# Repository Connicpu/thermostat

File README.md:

# Thermostat V3

Shared as-is — not seeking contributions or pull requests.

ESP32-C6 Zigbee thermostat for single-stage HVAC (R/C/W/Y/G), with e-paper display, SHT40 temperature/humidity sensor, and triac outputs. Designed for JLCPCB assembly.

## Gallery

On-device screens (296×128 e-paper, shown at 2×; °F):

| Home | Menu |
|---|---|
|  |  |
| **Schedule** | **Boost to** |
|  |  |

Home Assistant Lovelace card ([install](firmware/ha/lovelace-card/README.md)):

| Heat, day (light) | Cool, night (dark) | Timed heat boost (dark) |
|---|---|---|
|  |  |  |

More: case renders in [case/](case/), every menu screen in [firmware/README.md](firmware/README.md).

## Case

The case (`case/thermostat_case.scad`) is a 147 × 71 × 26.25 mm PETG shell, backplate, and panel carrier for a Bambu P2S with a 0.4 mm nozzle. The carrier holds the display panel with its nominal back 4.45 mm above the board. The panel rests on stops 0.15 mm under that, located by the long-edge fences and the cable-end posts. Four bridges in the shell press the border. The flex plugs into J4 with the display panel seated on the stops. A thin corner can leave J4; the shell comes off, the tail is pressed back in, and the slider is closed. A fingernail shuts the slider on the ear's +x face, and a fingertip on the carrier push opens it toward +x. The shell clips to the backplate. It does not clamp the board. The three buttons snap into the face from the inside and stay in the shell. Each cap is a 65° cone and one 0.40 mm leaf. The leaf is a cantilever, free length 4.35 mm, and it only keeps the cap in the face. The print adds a 0.34 mm nub on the cone top under the free end so the leaf's bed-facing face is a bridge, and that nub is snapped off before the cap goes into the tube. [case/ASSEMBLY.md](case/ASSEMBLY.md) is the build order, the fold dimensions, and the service steps.

Air inside the case is split into three zones:

- **Hot zone** (left). The triacs, the opto drive side, the buck, and the bridge. Slots in the bottom edge and the lower left wall let room air in. Matching slots in the top edge and the upper left wall let it out. A front curtain just left of the display keeps that air from spilling under the panel.
- **Middle zone.** The ESP32-C6, the display, and the wiring hole. This zone has no vents of its own. Close the hole in the wall around the cable with a printed PETG plug so that air stays in the middle zone.
- **Sensor duct** (right). The SHT40 island. Bottom-edge slots and a band of slots on the right wall feed it. The top-edge slots and the front island slots exhaust it. Two ribs on the backplate and a partition in the shell separate it from the middle zone. The backplate under the island is solid, because slots there would face the drywall and open the duct onto the wall.

The ribs stop 0.4 mm short of the board, and above the lip they run out to the lip's outer face so they come within 0.3 mm of the shell. The zone walls keep at least 0.5 mm off the parts, including the USB-C shield legs and locating peg on the back of the board. Front clearances include the ±0.16 mm board-thickness tolerance.

**Expected benefit.** A zonal model puts the triac-induced sensor rise about **10–25% lower** than the same case with one undivided cavity (no ribs, partition, or curtain). That is a model, not a measurement. Most of the remaining error is heat flowing along the PCB ground pour, which a case cannot stop, and the vents themselves carry only a small share of the hot zone's heat. The walls matter more than the hole count: they also help keep wall-cavity air from the wiring hole away from the sensor.

**Check it.** Log a heat call and a cool call against a reference thermometer, with a clamp meter on W, Y, and G. Taping the edge slots removes only the vents, about 6% of the modeled sensor rise; the ribs, partition, and curtain stay, so expect little difference. Measuring what the walls do needs a second print without the ribs, partition, and curtain. The two offsets add, so use only one. `CONFIG_THERMO_SELF_HEAT_OFFSET_C100` is build-time (`menuconfig`, then a reflash) and defaults to 0. ZHA sets the thermostat's LocalTemperatureCalibration attribute, in 0.1 °C steps over ±2.5 °C, applied on top of that build-time offset. About −0.1 °C is an unmeasured guess until a reference-thermometer log exists.

`board.stl` is not in the repo. From the repo root, export the populated board with KiCad 9 (do not pass `--drill-origin`; `scripts/case_fit.py` places the model):

```
kicad-cli pcb export stl -o board.stl --force --cut-vias-in-body kicad/thermostat-v3.kicad_pcb
```

The script header also has the OpenSCAD lines for the assembly-frame `back.stl`, `shell.stl`, `carrier.stl`, and the seated and pressed button meshes it checks against. The flex fold, the tail insertion, the carrier clearances, and the button travel run even when `board.stl` is absent.

- kicad/: KiCad 9 project
- fab/: Gerbers plus JLC BOM/CPL
- part-plan.md: part choices, sources, cost estimate
- v2-original/: the previous V2 design

Warning: don't connect USB while 24VAC is wired unless you use a USB isolator.
First-time flashing on Arch Linux: [docs/flashing-arch.md](docs/flashing-arch.md).

This project is shared as-is. It is not seeking contributions or pull requests.

## License

MIT — see [LICENSE](LICENSE). Third-party notices (Lit, Material Design Icons, DejaVu/Bitstream,
Espressif, Good Display sequences, LCSC STEP models, …) are in [NOTICE](NOTICE).

## Security

This is a DIY thermostat that switches 24 VAC HVAC loads. Treat the Zigbee network perimeter as
the security boundary:

- **OTA is unsigned.** The device accepts Zigbee OTA images and installs them with `esp_ota_*`
  (rollback via pending-verify exists). Anyone who can run an OTA server the device trusts can
  push firmware. There is no image signature check.
- **Join policy is open.** `install_code_policy` is false, so pairing uses the Zigbee 3.0
  well-known trust-center link-key path (normal for Home Assistant / ZHA). Don't leave the
  network open to joining when you aren't pairing.
- **USB Serial/JTAG console** is enabled in `sdkconfig.defaults`. Physical USB access to the
  board gives a console.
- Factory reset from the on-device menu is intentional.

See also [MANUFACTURER_ID.md](MANUFACTURER_ID.md) for the Zigbee manufacturer code (`0x434E`:
this project's DIY code from the quiet `0x3000`–`0x5FFF` band; not CSA-assigned, not certified).

## Third-party / display provenance

E-paper driver sequences in `firmware/components/display/ssd1680.c` follow Good Display's
GDEY029T94 sample/datasheet (not a verbatim copy of their sample tree). Full attribution is
in [NOTICE](NOTICE).

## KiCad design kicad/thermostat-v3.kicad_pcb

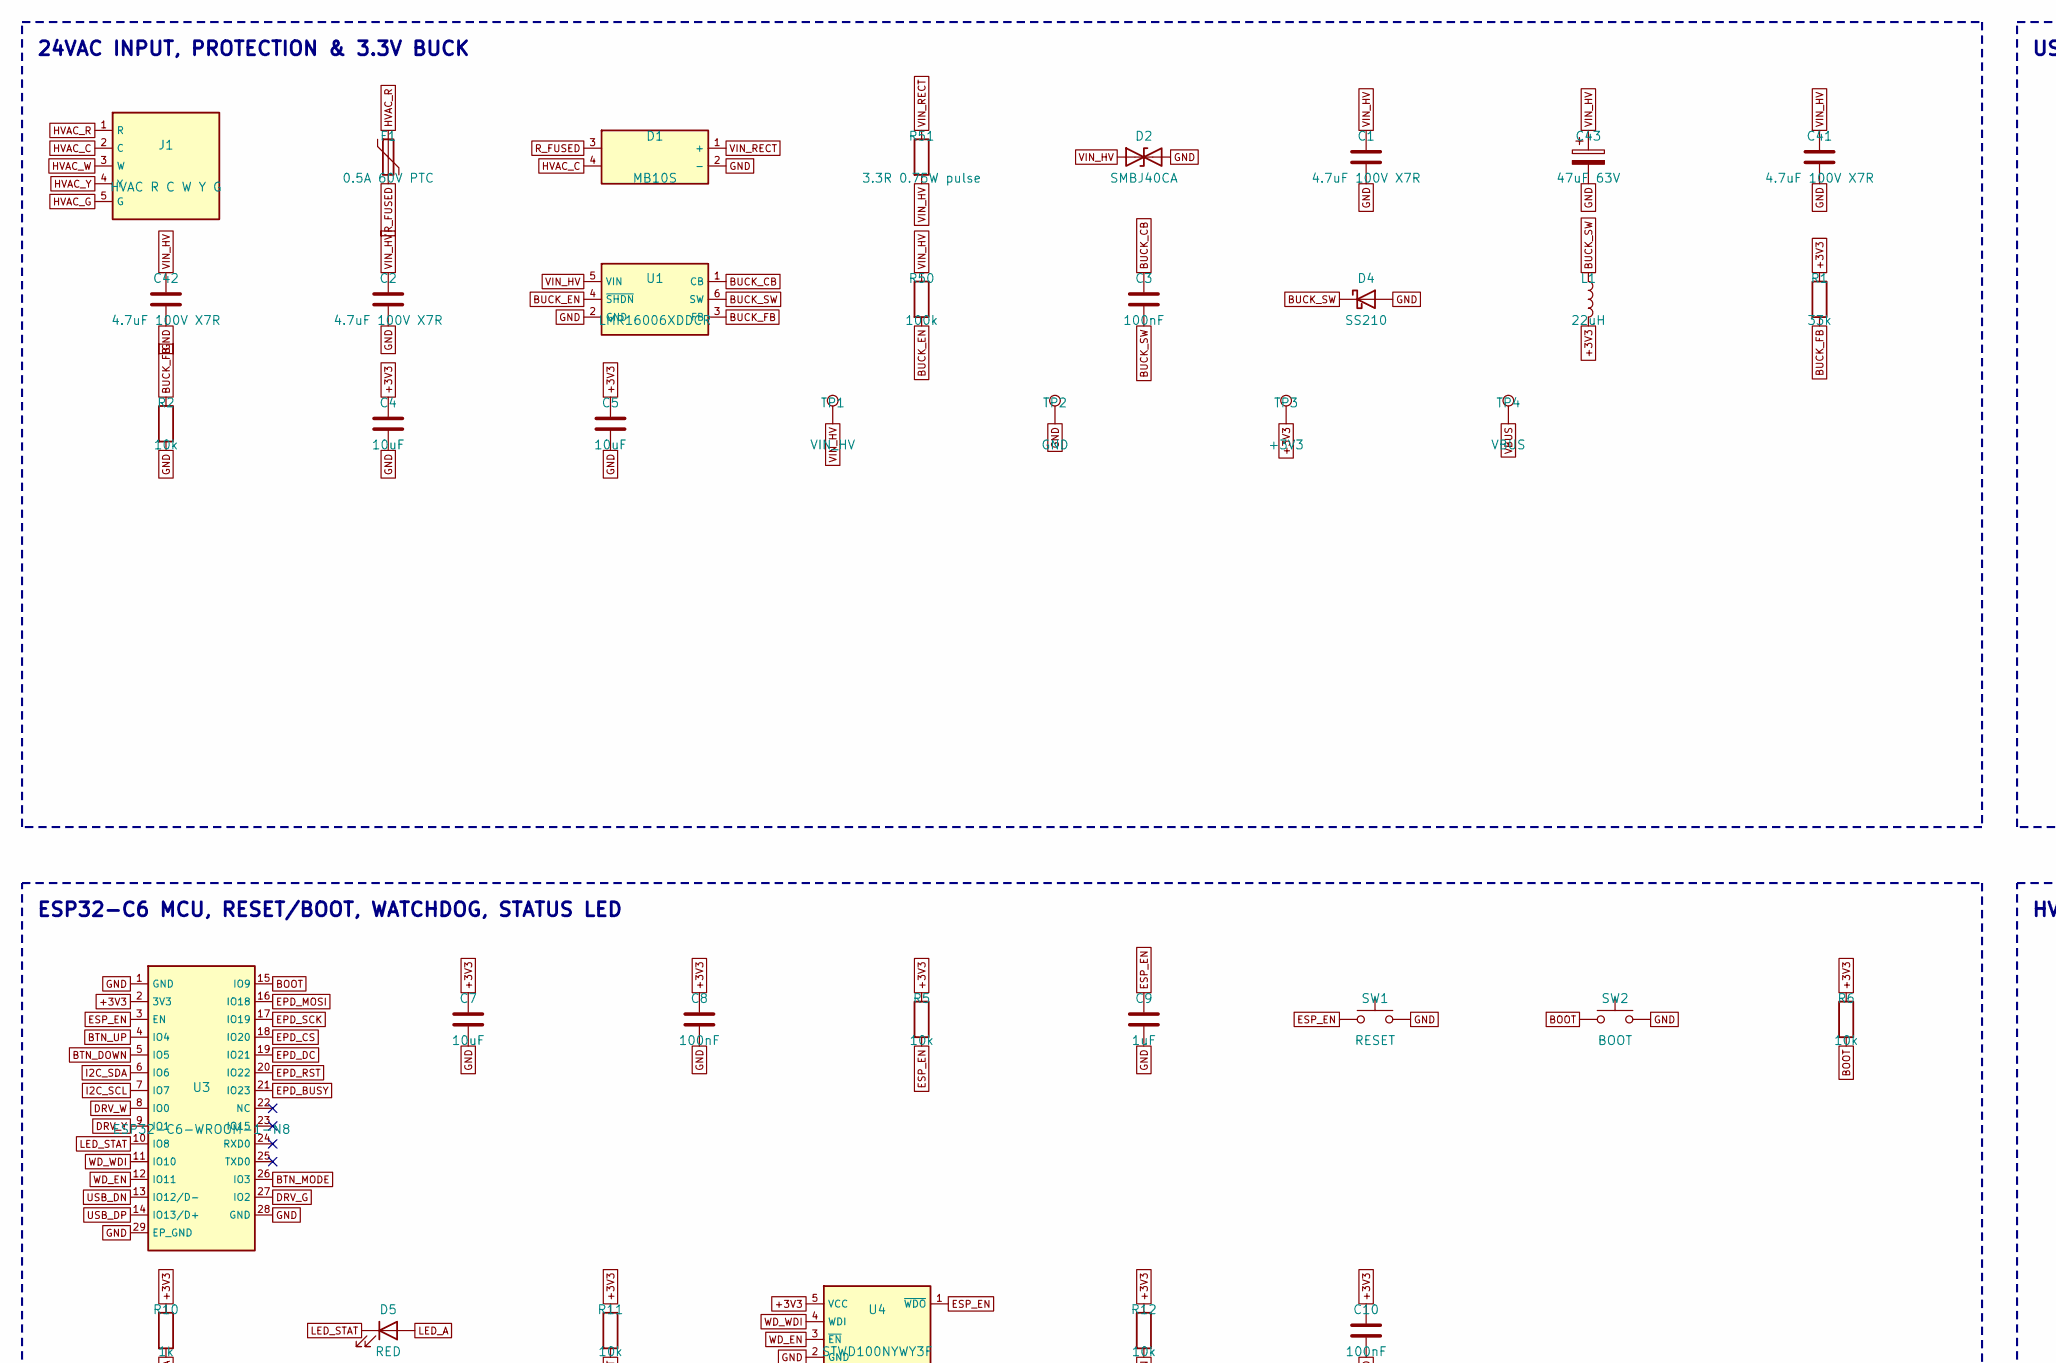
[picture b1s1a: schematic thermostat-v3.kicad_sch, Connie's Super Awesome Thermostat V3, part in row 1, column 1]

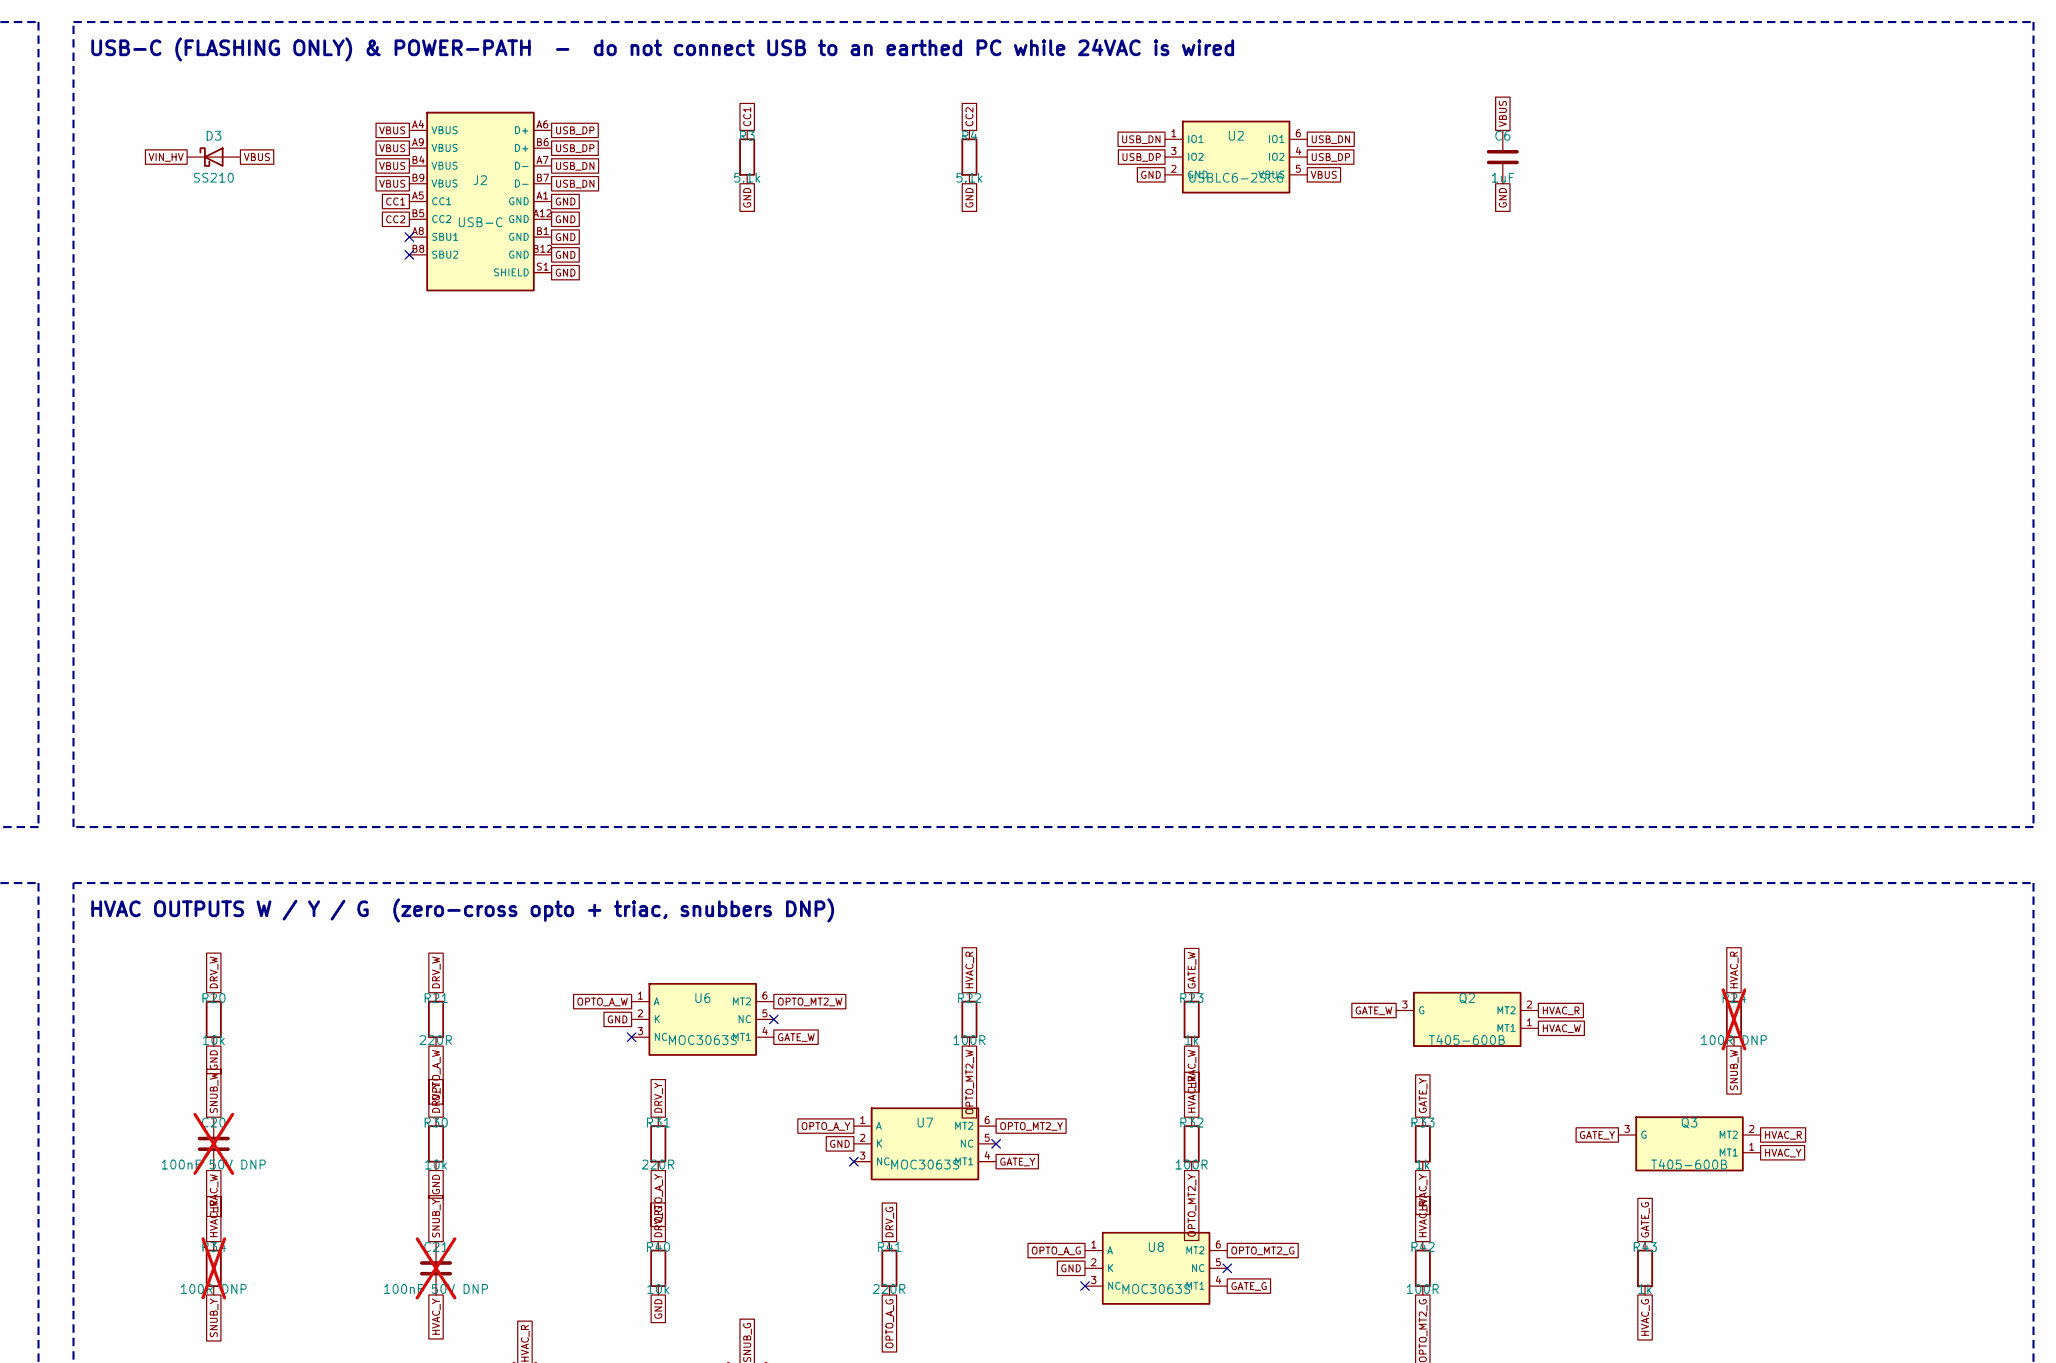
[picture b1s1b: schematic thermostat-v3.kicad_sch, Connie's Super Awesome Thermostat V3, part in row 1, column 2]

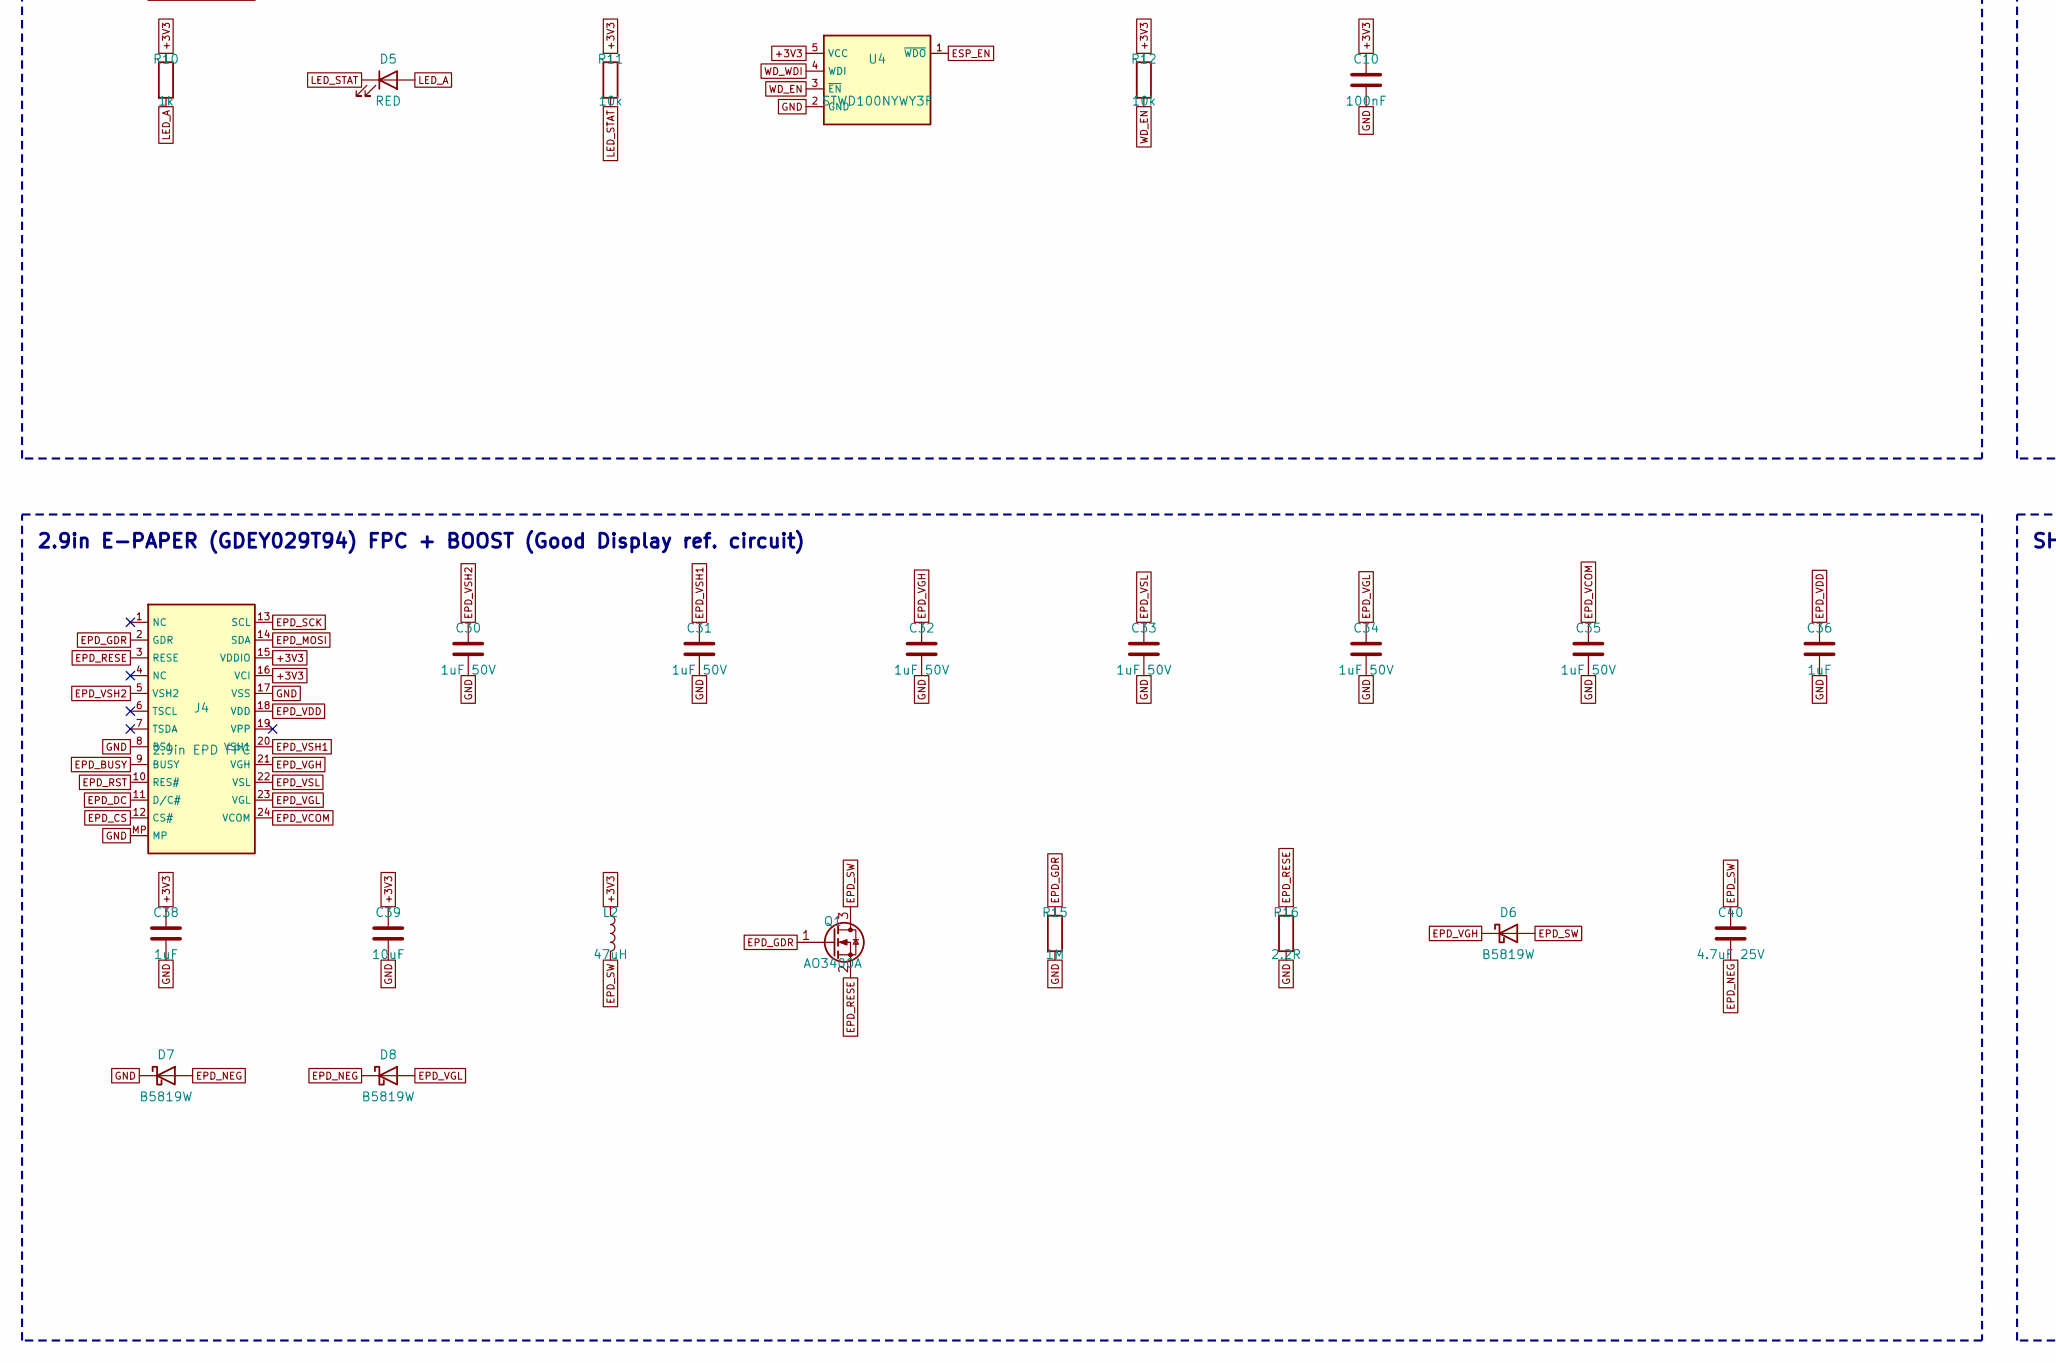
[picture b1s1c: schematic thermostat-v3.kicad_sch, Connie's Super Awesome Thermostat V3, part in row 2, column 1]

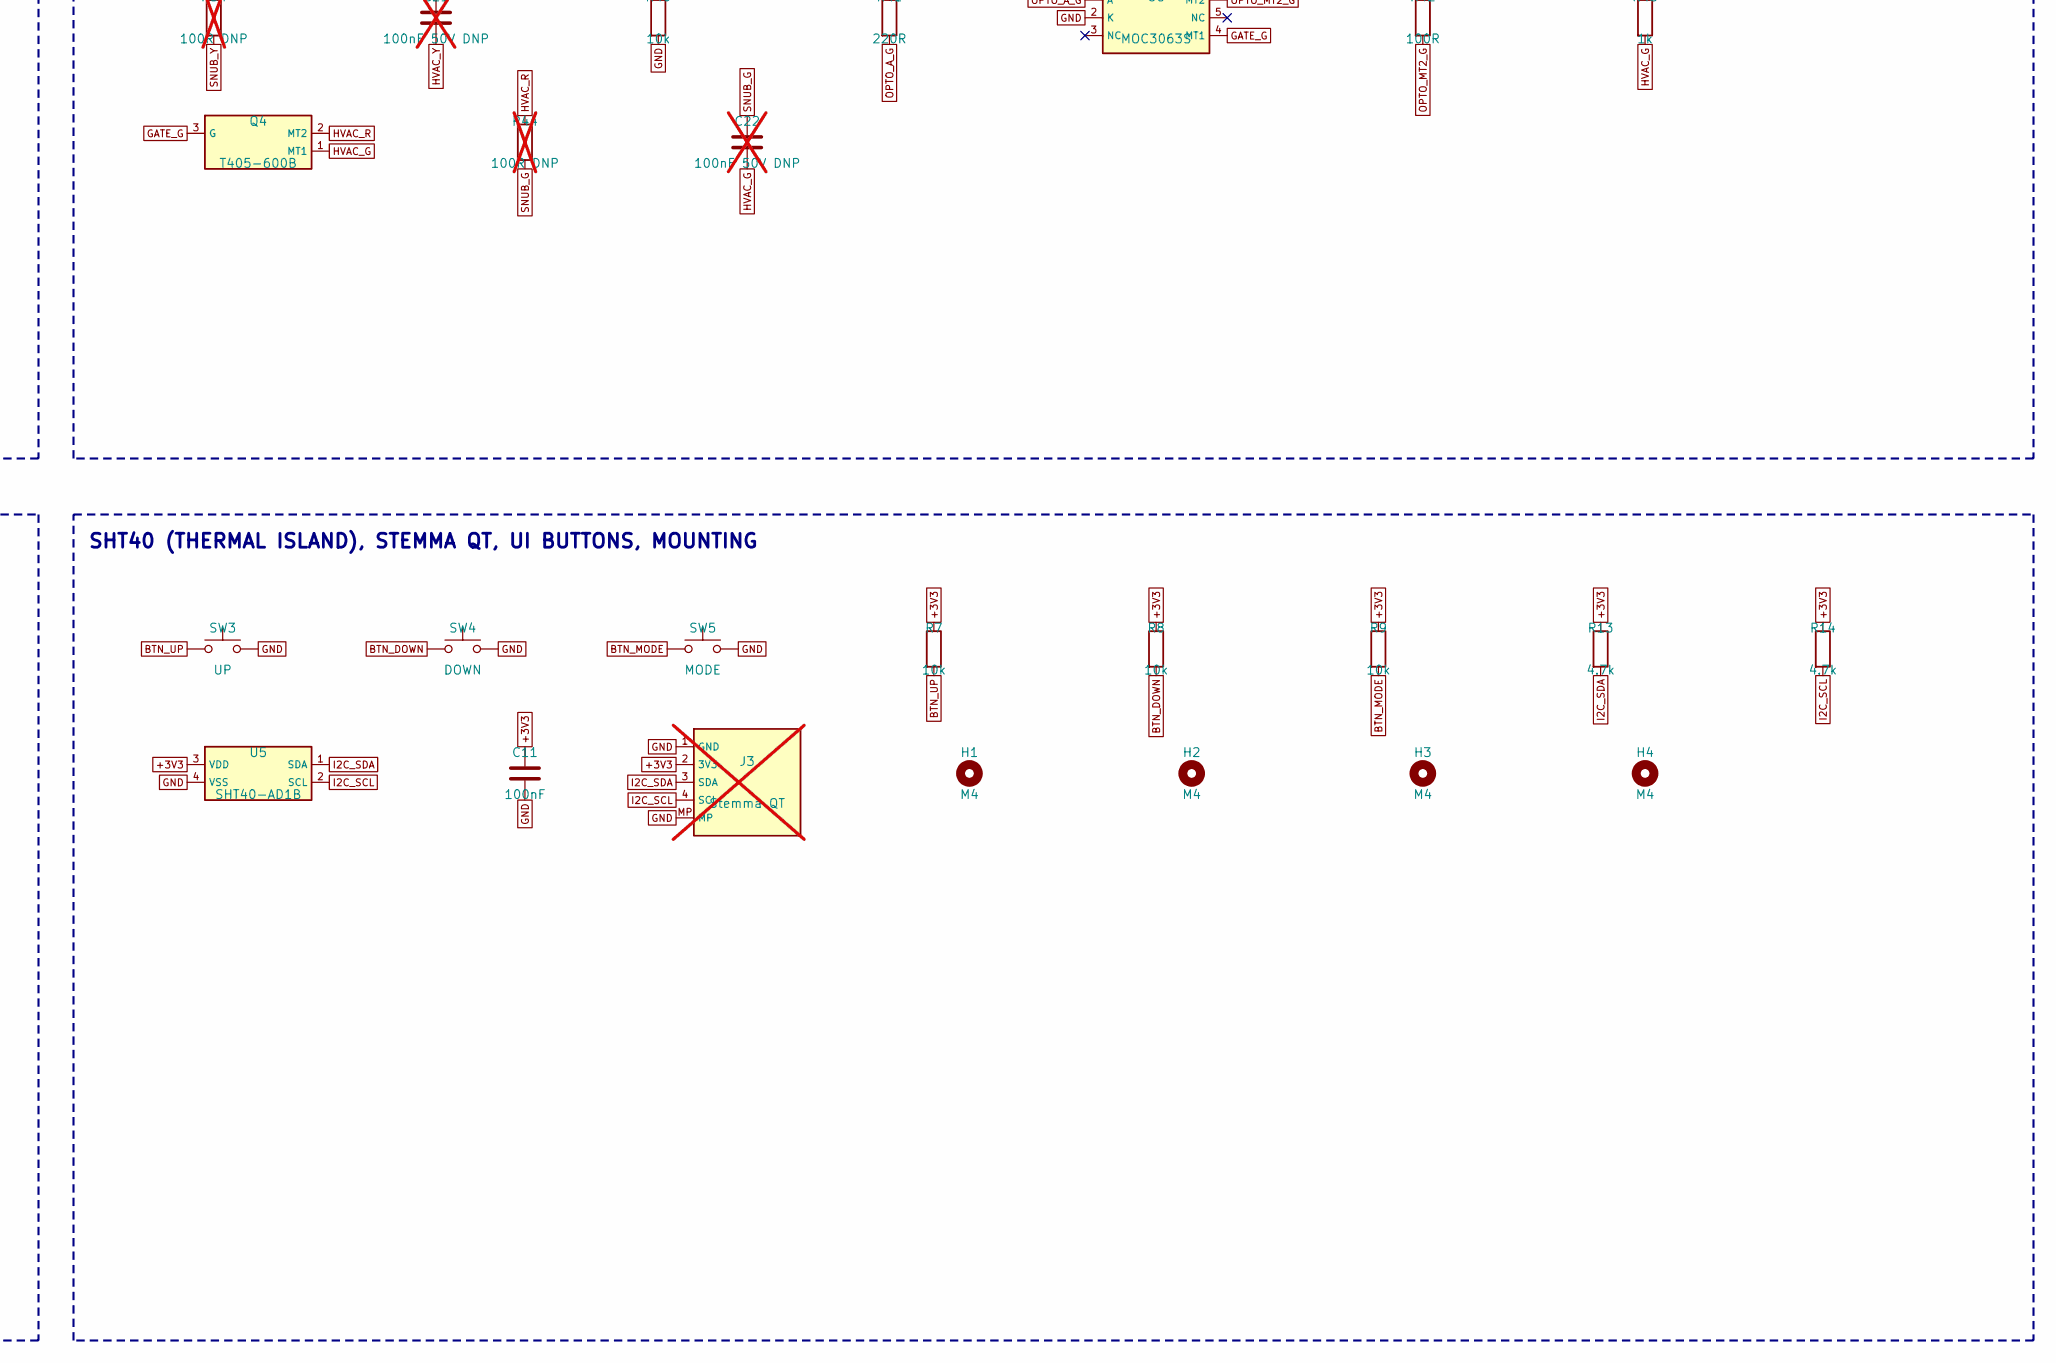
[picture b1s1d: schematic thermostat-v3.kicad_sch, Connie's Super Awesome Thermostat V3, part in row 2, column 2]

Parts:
C1, C2, C41, C42: 4.7uF 100V X7R; C_1210_3225Metric; MPN FS32X475K101EGG; LCSC C381466
C3, C8, C10, C11: 100nF; C_0402_1005Metric; LCSC C1525
C4, C5, C7, C39: 10uF; C_0603_1608Metric; LCSC C19702
C6, C9, C36, C38: 1uF; C_0402_1005Metric; LCSC C52923
C20, C21, C22: 100nF 50V DNP; C_0805_2012Metric; LCSC C49678; not fitted
C30, C31, C32, C33, C34, C35: 1uF 50V; C_0603_1608Metric; LCSC C15849
C40: 4.7uF 25V; C_0805_2012Metric; LCSC C1779
C43: 47uF 63V; CP_Radial_D8.0mm_P3.50mm; MPN JBLH2470M063D090RLM 8x9 THT, BACK side,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; LCSC C19270693
D1: MB10S; MBS_MB10S; LCSC C2488
D2: SMBJ40CA; D_SMB_TVS; MPN SMBJ40CA (bidirectional, JLC preferred-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; LCSC C19077590
D3: SS210; SMA_SS210; MPN SS210 100V 2A Schottky (was B5819W 40V); LCSC C14996
D4: SS210; SMA_SS210; LCSC C14996
D5: RED; LED_0603_KT; LCSC C2286
D6, D7, D8: B5819W; SOD-123_B5819W; LCSC C8598
F1: 0.5A 60V PTC; F1812_PTC; MPN mSMD050-60V; LCSC C70113
H1, H2, H3, H4: M4; MountingHole_4.3mm_M4
J1: HVAC R C W Y G; HVAC_TERM_15EDGRC; MPN 15EDGRC-3.5-05P-14-00A(H) right-angle, 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; LCSC C7603439
J2: USB-C; USB_C_Receptacle_HRO_TYPE-C-31-M-12; LCSC C165948
J3: Stemma QT; JST_SH4_STEMMA; LCSC C51940130; not fitted
J4: 2.9in EPD FPC; FPC24_AFC07; LCSC C262567
L1: 22uH; L_Sunlord_SWPA6045S; MPN SWPA6045S220MT 22uH Isat 2.2A 89mOhm (w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; LCSC C83454
L2: 47uH; L_APV_ANR3015; LCSC C7427088
Q1: AO3400A; SOT-23_AO3400A; LCSC C20917
Q2, Q3, Q4: T405-600B; TO-252-2_TRIAC_DPAK; MPN T405-600B-TR (ST T4 logic-level, IGT 5m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; LCSC C283473
R1: 33k; R_0402_1005Metric; LCSC C25779
R2, R5, R6, R7, R8, R9, R11, R12, R20, R30, R40: 10k; R_0402_1005Metric; LCSC C25744
R3, R4: 5.1k; R_0402_1005Metric; LCSC C25905
R10: 1k; R_0402_1005Metric; LCSC C11702
R13, R14: 4.7k; R_0402_1005Metric; LCSC C25900
R15: 1M; R_0402_1005Metric; LCSC C26083
R16: 2.2R; R_0603_1608Metric; LCSC C22939
R21, R31, R41: 220R; R_0402_1005Metric; LCSC C25091
R22, R32, R42: 100R; R_0805_2012Metric; LCSC C17408
R23, R33, R43: 1k; R_0805_2012Metric; LCSC C17513
R24, R34, R44: 100R DNP; R_0805_2012Metric; LCSC C17408; not fitted
R50: 100k; R_0402_1005Metric; MPN 0402WGF1003TCE; LCSC C25741
R51: 3.3R 0.75W pulse; R_1206_3216Metric; MPN CRCW12063R30FKEAHP (Vishay pulse-proof,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; LCSC C844038
SW1: RESET; SW_TS1187A; LCSC C318884
SW2: BOOT; SW_TS1187A; LCSC C318884
SW3: UP; SW_TS1187A; LCSC C318884
SW4: DOWN; SW_TS1187A; LCSC C318884
SW5: MODE; SW_TS1187A; LCSC C318884
TP1: VIN_HV; TestPoint_Pad_D1.5mm; MPN test pad
TP2: GND; TestPoint_Pad_D1.5mm; MPN test pad
TP3: +3V3; TestPoint_Pad_D1.5mm; MPN test pad
TP4: VBUS; TestPoint_Pad_D1.5mm; MPN test pad
U1: LMR16006XDDCR; SOT-23-6_LMR16006; LCSC C87080
U2: USBLC6-2SC6; SOT-23-6_USBLC6; LCSC C7519
U3: ESP32-C6-WROOM-1-N8; ESP32-C6-WROOM-1; LCSC C5366877
U4: STWD100NYWY3F; SOT-23-5_STWD100; LCSC C46043
U5: SHT40-AD1B; Sensirion_DFN-4_1.5x1.5mm_P0.8mm_SHT4x_NoCentralPad; LCSC C2909890
U6, U7, U8: MOC3063S; LCSC C77950

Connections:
+3V3: C4.1, C5.1, C7.1, C8.1, C10.1, C11.1, C38.1, C39.1, J3.2 (3V3), J4.15 (VDDIO), J4.16 (VCI), L1.2, L2.1, R1.1, R5.1, R6.1, R7.1, R8.1, R9.1, R10.1, R11.1, R12.1, R13.1, R14.1, TP3.1, U3.2 (3V3), U4.5 (VCC), U5.3 (VDD)
BOOT: R6.2, SW2.1, U3.15 (IO9)
BTN_DOWN: R8.2, SW4.1, U3.5 (IO5)
BTN_MODE: R9.2, SW5.1, U3.26 (IO3)
BTN_UP: R7.2, SW3.1, U3.4 (IO4)
BUCK_CB: C3.1, U1.1 (CB)
BUCK_EN: R50.2, U1.4 (~SHDN)
BUCK_FB: R1.2, R2.1, U1.3 (FB)
BUCK_SW: C3.2, D4.1 (K), L1.1, U1.6 (SW)
CC1: J2.A5 (CC1), R3.1
CC2: J2.B5 (CC2), R4.1
DRV_G: R40.1, R41.1, U3.27 (IO2)
DRV_W: R20.1, R21.1, U3.8 (IO0)
DRV_Y: R30.1, R31.1, U3.9 (IO1)
EPD_BUSY: J4.9 (BUSY), U3.21 (IO23)
EPD_CS: J4.12 (CS#), U3.18 (IO20)
EPD_DC: J4.11 (D/C#), U3.19 (IO21)
EPD_GDR: J4.2 (GDR), Q1.1 (G), R15.1
EPD_MOSI: J4.14 (SDA), U3.16 (IO18)
EPD_NEG: C40.2, D7.2 (A), D8.1 (K)
EPD_RESE: J4.3 (RESE), Q1.2 (S), R16.1
EPD_RST: J4.10 (RES#), U3.20 (IO22)
EPD_SCK: J4.13 (SCL), U3.17 (IO19)
EPD_SW: C40.1, D6.2 (A), L2.2, Q1.3 (D)
EPD_VCOM: C35.1, J4.24 (VCOM)
EPD_VDD: C36.1, J4.18 (VDD)
EPD_VGH: C32.1, D6.1 (K), J4.21 (VGH)
EPD_VGL: C34.1, D8.2 (A), J4.23 (VGL)
EPD_VSH1: C31.1, J4.20 (VSH1)
EPD_VSH2: C30.1, J4.5 (VSH2)
EPD_VSL: C33.1, J4.22 (VSL)
ESP_EN: C9.1, R5.2, SW1.1, U3.3 (EN), U4.1 (~WDO)
GATE_G: Q4.3 (G), R43.1, U8.4 (MT1)
GATE_W: Q2.3 (G), R23.1, U6.4 (MT1)
GATE_Y: Q3.3 (G), R33.1, U7.4 (MT1)
GND: C1.2, C2.2, C4.2, C5.2, C6.2, C7.2, C8.2, C9.2, C10.2, C11.2, C30.2, C31.2, C32.2, C33.2, C34.2, C35.2, C36.2, C38.2, C39.2, C41.2, C42.2, C43.2, D1.2 (-), D2.2 (A2), D4.2 (A), D7.1 (K), J2.A1 (GND), J2.A12 (GND), J2.B1 (GND), J2.B12 (GND), J2.S1 (SHIELD), J3.1 (GND), J3.MP, J4.8 (BS1), J4.17 (VSS), J4.MP, R2.2, R3.2, R4.2, R15.2, R16.2, R20.2, R30.2, R40.2, SW1.2, SW2.2, SW3.2, SW4.2, SW5.2, TP2.1, U1.2 (GND), U2.2 (GND), U3.1 (GND), U3.28 (GND), U3.29 (EP_GND), U4.2 (GND), U5.4 (VSS), U6.2 (K), U7.2 (K), U8.2 (K)
HVAC_C: D1.4, J1.2 (C)
HVAC_G: C22.2, J1.5 (G), Q4.1 (MT1), R43.2
HVAC_R: F1.1, J1.1 (R), Q2.2 (MT2), Q3.2 (MT2), Q4.2 (MT2), R22.1, R24.1, R32.1, R34.1, R42.1, R44.1
HVAC_W: C20.2, J1.3 (W), Q2.1 (MT1), R23.2
HVAC_Y: C21.2, J1.4 (Y), Q3.1 (MT1), R33.2
I2C_SCL: J3.4 (SCL), R14.2, U3.7 (IO7), U5.2 (SCL)
I2C_SDA: J3.3 (SDA), R13.2, U3.6 (IO6), U5.1 (SDA)
LED_A: D5.2 (A), R10.2
LED_STAT: D5.1 (K), R11.2, U3.10 (IO8)
OPTO_A_G: R41.2, U8.1 (A)
OPTO_A_W: R21.2, U6.1 (A)
OPTO_A_Y: R31.2, U7.1 (A)
OPTO_MT2_G: R42.2, U8.6 (MT2)
OPTO_MT2_W: R22.2, U6.6 (MT2)
OPTO_MT2_Y: R32.2, U7.6 (MT2)
R_FUSED: D1.3, F1.2
SNUB_G: C22.1, R44.2
SNUB_W: C20.1, R24.2
SNUB_Y: C21.1, R34.2
USB_DN: J2.A7 (D-), J2.B7 (D-), U2.1 (IO1), U2.6 (IO1), U3.13 (IO12/D-)
USB_DP: J2.A6 (D+), J2.B6 (D+), U2.3 (IO2), U2.4 (IO2), U3.14 (IO13/D+)
VBUS: C6.1, D3.2 (A), J2.A4 (VBUS), J2.A9 (VBUS), J2.B4 (VBUS), J2.B9 (VBUS), TP4.1, U2.5 (VBUS)
VIN_HV: C1.1, C2.1, C41.1, C42.1, C43.1, D2.1 (A1), D3.1 (K), R50.1, R51.2, TP1.1, U1.5 (VIN)
VIN_RECT: D1.1 (+), R51.1
WD_EN: R12.2, U3.12 (IO11), U4.3 (~EN)
WD_WDI: U3.11 (IO10), U4.4 (WDI)

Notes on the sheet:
24VAC INPUT, PROTECTION & 3.3V BUCK
USB-C (FLASHING ONLY) & POWER-PATH - do not connect USB to an earthed PC while 24VAC is wired
ESP32-C6 MCU, RESET/BOOT, WATCHDOG, STATUS LED
HVAC OUTPUTS W / Y / G (zero-cross opto + triac, snubbers DNP)
2.9in E-PAPER (GDEY029T94) FPC + BOOST (Good Display ref. circuit)
SHT40 (THERMAL ISLAND), STEMMA QT, UI BUTTONS, MOUNTING

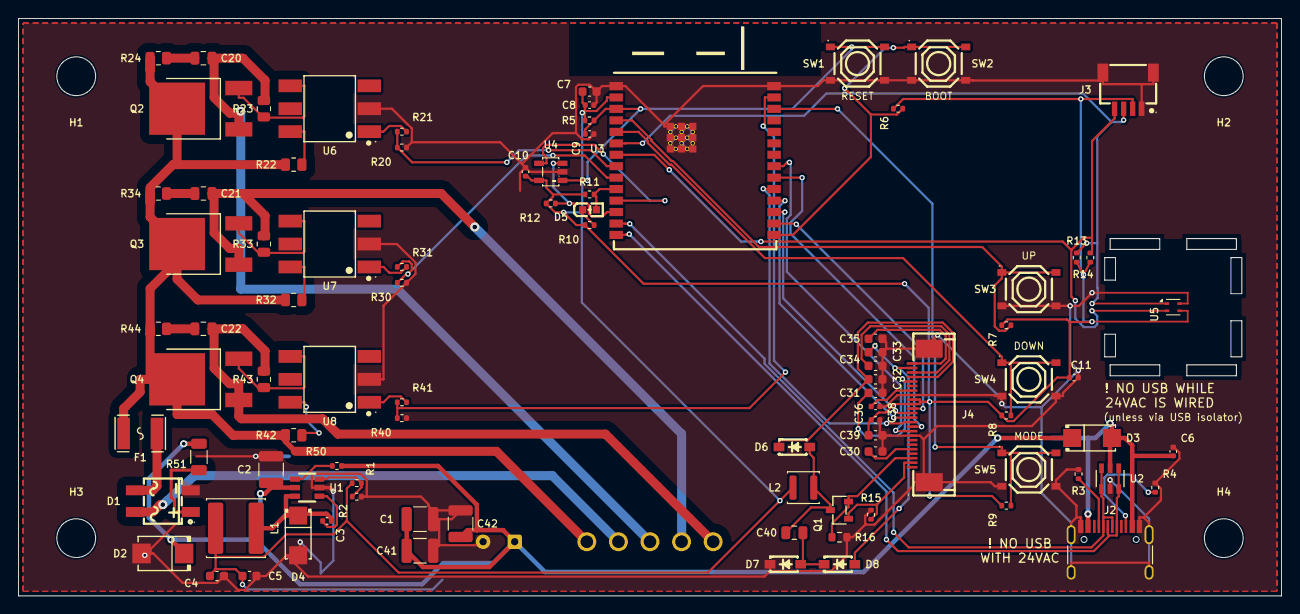
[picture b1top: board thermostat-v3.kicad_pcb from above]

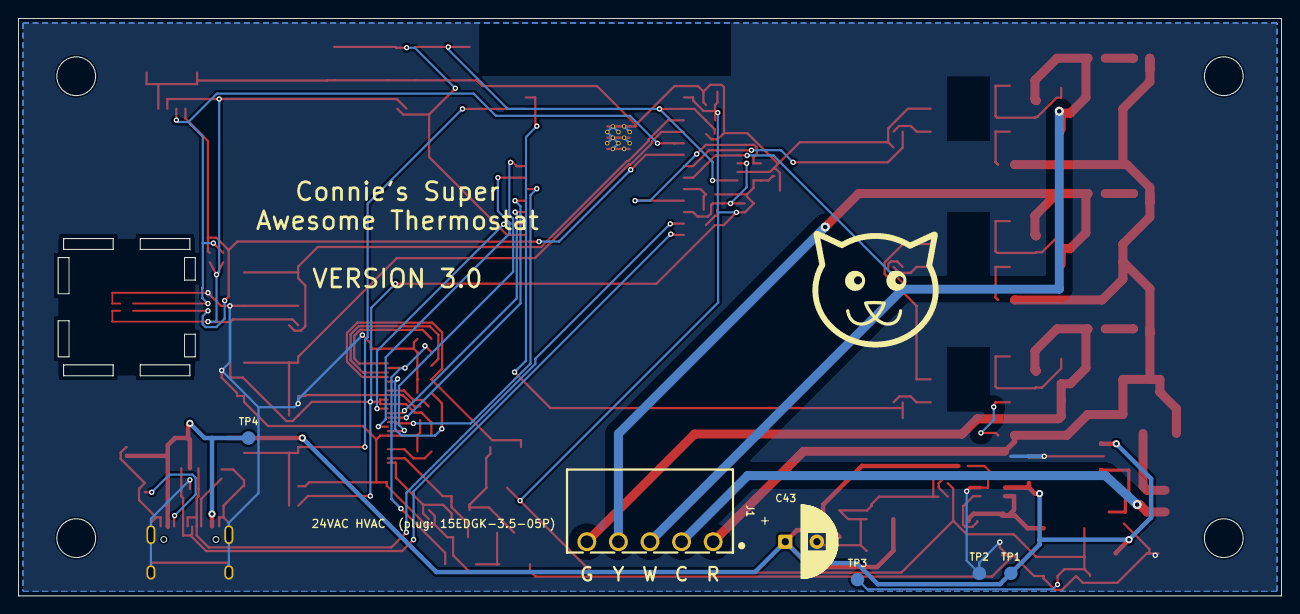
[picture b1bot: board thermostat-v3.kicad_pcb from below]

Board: 2 copper layers, 140.0 x 64.0 mm, 101 parts (7 on the bottom side), 62 nets.

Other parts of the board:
LOGO1: LOGO; LOGO_CAT

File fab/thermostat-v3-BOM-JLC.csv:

Comment,Designator,Footprint,LCSC Part #
220R,"R21,R31,R41",R_0402_1005Metric,C25091
4.7uF 25V,C40,C_0805_2012Metric,C1779
47uH,L2,L_APV_ANR3015,C7427088
1uF 50V,"C30,C31,C32,C33,C34,C35",C_0603_1608Metric,C15849
AO3400A,Q1,SOT-23_AO3400A,C20917
T405-600B,"Q2,Q3,Q4",TO-252-2_TRIAC_DPAK,C283473
10k,"R2,R5,R6,R7,R8,R9,R11,R12,R20,R30,R40",R_0402_1005Metric,C25744
10uF,"C4,C5,C7,C39",C_0603_1608Metric,C19702
100nF,"C3,C8,C10,C11",C_0402_1005Metric,C1525
SS210,"D3,D4",SMA_SS210,C14996
1uF,"C6,C9,C36,C38",C_0402_1005Metric,C52923
TS-1187A-B-A-B,"SW1,SW2,SW3,SW4,SW5",SW_TS1187A,C318884
33k,R1,R_0402_1005Metric,C25779
LMR16006XDDCR,U1,SOT-23-6_LMR16006,C87080
1k,"R23,R33,R43",R_0805_2012Metric,C17513
USB-C,J2,USB_C_Receptacle_HRO_TYPE-C-31-M-12,C165948
100R,"R22,R32,R42",R_0805_2012Metric,C17408
ESP32-C6-WROOM-1-N8,U3,ESP32-C6-WROOM-1,C5366877
5.1k,"R3,R4",R_0402_1005Metric,C25905
RED,D5,LED_0603_KT,C2286
4.7k,"R13,R14",R_0402_1005Metric,C25900
100k,R50,R_0402_1005Metric,C25741
STWD100NYWY3F,U4,SOT-23-5_STWD100,C46043
SHT40-AD1B,U5,Sensirion_DFN-4_1.5x1.5mm_P0.8mm_SHT4x_NoCentralPad,C2909890
4.7uF 100V X7R,"C1,C2,C41,C42",C_1210_3225Metric,C381466
2.9in EPD FPC,J4,FPC24_AFC07,C262567
MOC3063S,"U6,U7,U8",MOC3063S,C77950
2.2R,R16,R_0603_1608Metric,C22939
1M,R15,R_0402_1005Metric,C26083
B5819W,"D6,D7,D8",SOD-123_B5819W,C8598
MB10S,D1,MBS_MB10S,C2488
SMBJ40CA,D2,D_SMB_TVS,C19077590
0.5A 60V PTC,F1,F1812_PTC,C70113
1k,R10,R_0402_1005Metric,C11702
3.3R 0.75W pulse,R51,R_1206_3216Metric,C844038
22uH,L1,L_Sunlord_SWPA6045S,C83454
USBLC6-2SC6,U2,SOT-23-6_USBLC6,C7519
